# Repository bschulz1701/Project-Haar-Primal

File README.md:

# Project-Haar-Primal
A minimal temp/pressure/RH sensor designed for environmental monitoring. Built off the [Haar](https://github.com/NorthernWidget-Skunkworks/Project-Haar) system, developed by Bobby Schulz at Northern Widget 

# Repo Roadmap
#### [Documents](Documents/) 

General document and image storage for repo and README

#### [Hardware](Hardware/)

Current board files (Eagle), Bill of Materials (BoM), and other design documents

#### [Production](Production/)

Contains the various Gerber and pick and place files required to have the Printed Circuit Boards (PCBs) manufactured or populated 

#### [Software](Software/)

The software associated with the piece of hardware, this is usually diagnostic software used for verifying or investigating the hardware

#### [Mechanical](Mechanical/)

Mechanical design files and assembly documents

<!-- #### [Testing](Testing/)

Scripts and results from the testing process and development process. Contains more detailed information about documented issues among other testing. 
 -->

## Overview
* **Type:** Sensor
* **Interfaces:** I<sup>2</sup>C
* **Release Version:** v2.0 - 2022/03/17

<!--  -->

## Features
### On-Board
* Selectable Pullups
* Reverse Polarity Protection  

### Interface
* I<sup>2</sup>C
* M12 circular connector 

<picture>
  <source media="(prefers-color-scheme: dark)" srcset="Documents/Pinout_LIGHT.png">
  
</picture>

## Specifications
* **Voltage - Supply:** 3.3V
* **Voltage - Logic:** 3.3V
* **Input Current (Avg, 1s period): 30.95&mu;A @ 3.3V**
* **Input Current (Avg, 5s period): 107.43&mu;A @ 3.3V**
* **Input Current (Max): 0.45mA @ 3.3V**

#### Sensor
**Temperature** [^1]
* Range: -40 ~ 125°C 
* Accuracy: &plusmn; 0.2°C
* Repeatability: &plusmn; 0.04°C

**Pressure** [^2]
* Range: 300 ~ 1200 hPa  
* Accuracy: &plusmn; 1 hPa
* Repeatability: &plusmn; 0.06 hPa

**Humidity** [^1]
* Range: 0 ~ 100%
* Accuracy: &plusmn; 2%
* Repeatability: 0.08%

[^1]: [SHT31 Datasheet](https://sensirion.com/media/documents/213E6A3B/63A5A569/Datasheet_SHT3x_DIS.pdf)
[^2]: [DPS368 Datasheet](https://www.infineon.com/dgdl/Infineon-DPS368-DS-v01_00-EN.pdf?fileId=5546d46269e1c019016a0c45105d4b40)

## Version History

`v0.0` - Initial primal version with screw terminal

`v0.1` - Initial 'hard mount' version, using M12 connector

`v1.0` - Removed pullup select[^3], added logic level buffer and voltage reg on input

`v1.1` - Moved via away from connector pads to prevent bridging when soldering 

`v2.0` - Fixed issue with address select jumper[^3]

## Jumper Settings 

> [!IMPORTANT]
> Jumper settings valid for version `v2.0` and beyond[^3]

[^3]: See Errata

**Configuration Jumpers**
| Jumper | Purpose | Open | Closed | Default | 
| ------ | ------- | ---------- | ---------- | ----- | 
| `JP1` | I<sup>2</sup>C Address Select | Base Address<sup>&dagger;</sup> | Alt Address<sup>&Dagger;</sup> | Open |

&dagger; SHT31 = `0x44`, DPS368 = `0x76`

&Dagger; SHT31 = `0x44`, DPS368 = `0x77`

## Known Issues/Errata

#### Solder Jumper Stencil

**Version Affected:** All

**Issue:** Depending on the thickness of the solder stencil used for populating the board, the solder jumpers may not bridge when desired. This is due to lack of stencil thickness specification and pad geometry.

**Workaround:** Make a note on the board assembly (if working with a board house) as to which jumpers should be connected (see jumper tables). Otherwise, if assembling manually, check the jumpers are connected, and bridge them using solder wire and a soldering iron if they have failed to jump where desired. 

#### Pullup Jumper

**Version Affected:** `v0.0`

**Issue:** Due to the resistor configuration with the solder jumper, if the jumper is left open, the resistors form a voltage divider which pulls down the I<sup>2</sup>C rails and causes a variety of bus failures.

**Workaround:** Leave jumper closed on device, this will pull the lines up to the 3.3V rail and prevent the issue 

**Resolution:** Fixed in version `v0.1` and beyond  

#### Address Jumper

**Version Affected:** `v0.1` to `v1.1`

**Issue:** `SDO` pin on DSP368 was erroniously left floating, meaning the DPS368 is continually fixed at the address of `0x76` and will not be effected by the address jumper status

**Workaround:** Leave jumper closed on device, this will hold the SHT31 at the default address as well and keep the address combination consistent 

**Resolution:** Fixed in version `v2.0` and beyond

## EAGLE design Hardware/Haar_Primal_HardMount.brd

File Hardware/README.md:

# Hardware Overview - Project Hyena

## Files

<!-- * [Legacy](Legacy/) - File storage for older hardware versions   -->
* Haar_Primal.sch - Eagle Schematic
* Haar_Primal.brd - Eagle Board File
* [Haar_Primal_0v0_DimensionalDrawing.pdf](Haar_Primal_0v0_DimensionalDrawing.png) - Mechanical Drawing
<!-- * [PrimaryLogger_BoM.csv](PrimaryLogger_BoM.csv) - BoM (For reference only, see [Production](../Production) for production ready BoM) -->
<!-- * [PrimaryLogger.pdf](PrimaryLogger_0v2.pdf) - PDF of Schematic  -->

## I2C Addresses 

| Device | Address | 
| ------ | ------- | 
| DPS368 | 0x77 | 
| SHT30 | 0x44 |

<!-- ## Pinout

| Particle Pin | Hyena Pin Name | Control | Function | 
| ------------ | -------------- | ------- | -------- |
| 8 | `3V3_EXT_EN` | Output | Enables the external 3.3v rail (active high, nominally low) | 
| 7 | `WD_HOLD` | Output | Controls the hardware watchdog timer, pulse high to "feed" timer |
| 6 | `GPIO1D` | IO | General digital IO pin for external sensors (J1 Connector) | 
| 5 | `GPIO2D` | IO | General digital IO pin for external sensors (J2 Connector) | 
| 4 | `GPIO3D` | IO | General digital IO pin for external sensors (J3 Connector) | 
| 3 | `RTC_INT` | Input | Interrupt line from RTC, natively high active low (open drain), triggers on falling edge |
| 2 | `SDA_CTRL` | Output | Used to turn internal I2C on or off (active high, I2C_OB on, natively low) |
| 1 | `SCL` | Output | I2C clock line |
| 0 | `SDA` | IO | I2C Data line |
| 9 | `3V3_SD_EN` | Output | Enable line for SD card 3.3v supply (active high, natively low) |
| 10 | `IO_EXP_INT` | Input | Global interrupt from the IO expander (functionality configurable via software) |
| 11 | `MISO` | Input | MasterInSlaveOut, part of SPI bus |
| 12 | `MOSI` | Output | MasterOutSlaveIn, part of SPI bus | 
| 13 | `SCK` | Output | SerialClocK, part of SPI bus | 
| 14 | `SD_CS` | Output | SD chip select line, active low |
| 15/ADC4 | `TIP` | IO | Designed as tipping bucket rain gauge input, connected to J6, pulled high by default |
| 16/ADC3 | `GPIOXA` | IO | Intended as analog input for potentiometric input (J5) |
| 17/ADC2 | `GPIO1A` | IO | General digital/analog IO pin for external sensors (J1 Connector) |
| 18/ADC1 | `GPIO2A` | IO | General digital/analog IO pin for external sensors (J2 Connector) |
| 19/ADC0 | `GPIO3A` | IO | General digital/analog IO pin for external sensors (J3 Connector) |

| IO Expander Pin | Hyena Pin Name | Control | Function |
| --------------- | -------------- | ------- | -------- |
| 0 | `3V3_EXT_FAULT` | Input | Monitor pin for external 3v3 rail, if over current trip, pin is pulled low, natively high |
| 1 | `3V3_SD_FAULT` | Input | Monitor pin for SD card 3v3 rail, if over current trip, pin is pulled low, natively high |
| 2 | `SD_CD` | Input | Card detect pin for SD card, natively high, pulled low to indicate physical presence of SD card | 
| 3 | `I2C_EXT_EN` | Output | Control line for external I2C buffer, natively high (on), can be pulled low to turn off the external I2C bus | 
| 4 | `PAR_INT` | Input | Event interrupt line from TCS3400 light sensor (used for PAR measurement), active low interrupt |

## Hardware Testing:
See Testing sub folder -->

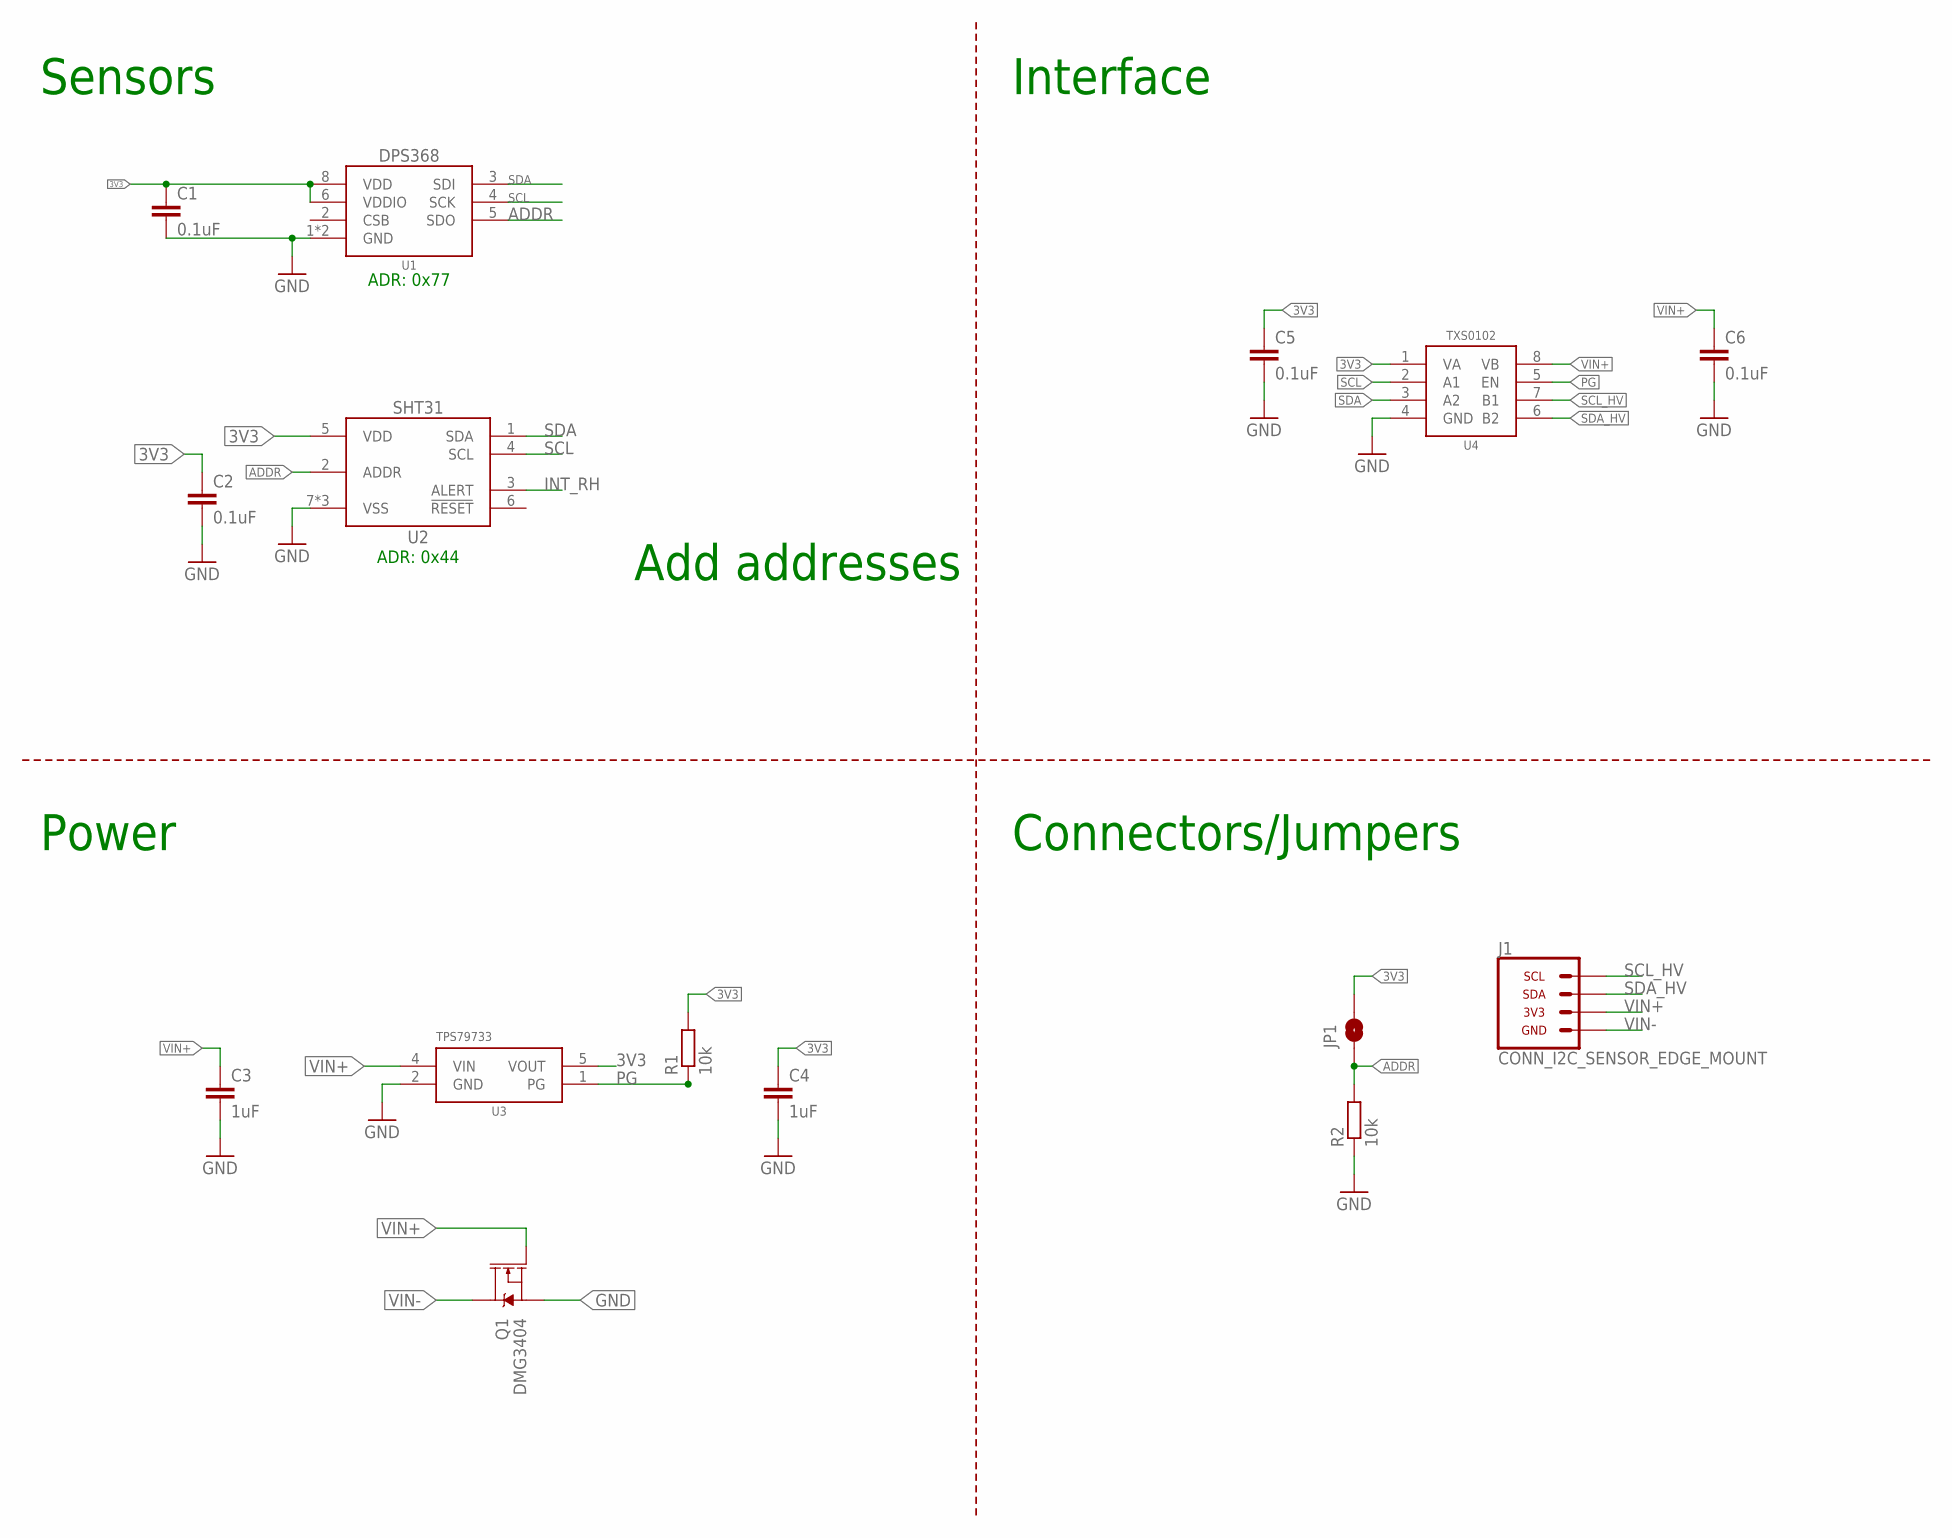
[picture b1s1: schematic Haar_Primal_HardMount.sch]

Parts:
C1, C2, C5, C6: 0.1uF; C0603
C3, C4: 1uF; C0603
J1: CONN_I2C_SENSOR_EDGE_MOUNT; SOLDERCUP_CONN_QUAD
JP1: JUMPER-SMT_2_NO_SILK; SMT-JUMPER_2_NO_SILK
Q1: DMG3404; SOT23-3
R1, R2: 10k; R0603
U1: DPS368; PG-VLGA-8
U2: SHT31DFN; DFN_8_2.5X2.5
U3: TPS79733; DCK_R-PDSO-G5
U4: TXS0102DQM; DQM_R-PX2SON-N8

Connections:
3V3: C1.1, C2.1, C4.1, C5.1, JP1.2, R1.2, U1.6 (VDDIO), U1.8 (VDD), U2.5 (VDD), U3.5 (VOUT), U4.1 (VA)
ADDR: JP1.1, R2.2, U1.5 (SDO), U2.2 (ADDR)
GND: C1.2, C2.2, C3.2, C4.2, C5.2, C6.2, Q1.2 (S), R2.1, U1.1 (GND), U1.7 (GND), U2.7 (VSS), U2.8 (VSS), U2.EP (VSS), U3.2 (GND), U4.4 (GND)
INT_RH: U2.3 (ALERT)
PG: R1.1, U3.1 (PG), U4.5 (EN)
SCL: U1.4 (SCK), U2.4 (SCL), U4.2 (A1)
SCL_HV: J1.3 (SCL), U4.7 (B1)
SDA: U1.3 (SDI), U2.1 (SDA), U4.3 (A2)
SDA_HV: J1.1 (SDA), U4.6 (B2)
VIN+: C3.1, C6.1, J1.2 (3V3), Q1.1 (G), U3.4 (VIN), U4.8 (VB)
VIN-: J1.4 (GND), Q1.3 (D)

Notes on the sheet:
Sensors
Interface
Power
Connectors/Jumpers
Add addresses
ADR: 0x44
ADR: 0x77

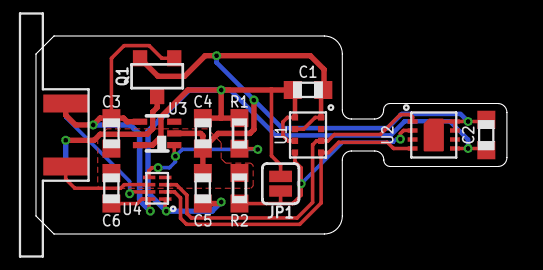
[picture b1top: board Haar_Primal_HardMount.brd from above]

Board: 2 copper layers, 26.2 x 11.0 mm, 15 parts (0 on the bottom side), 10 nets.

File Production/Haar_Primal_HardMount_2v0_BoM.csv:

"Qty","Value","Device","Package","Parts","Description","DIGIKEY","DISP","MF","MPN","VALUE","VALUE_PART",
"4","0.1uF","C-EU0.1UFC0603","C0603","C1, C2, C5, C6","CAPACITOR, European symbol","490-6051-1-ND","","Murata","GCM188R71E104KA57D","","",
"2","10k","R-EU_100KR0603","R0603","R1, R2","RESISTOR, European symbol","311-100KHRCT-ND","","Yageo","RC0603FR-07100KL","","100k",
"2","1uF","C-EU1UFC0603","C0603","C3, C4","CAPACITOR, European symbol","587-1251-1-ND","","Yaiyo Yuden","EMK107BJ105KA-T","","",
"1","CONN_I2C_SENSOR_EDGE_MOUNT","CONN_I2C_SENSOR_EDGE_MOUNT","SOLDERCUP_CONN_QUAD","J1","GEMS Connector for I2C Devices - Sensor Side","A97650-ND","","TE Connectivity","1838893-2","","",
"1","DMG3404","MOSFET-NCH-DMG3404L","SOT23-3","Q1","N-channel MOSFETs","DMG3404L-7DICT-ND","","Diodes Incorporated","DMG3404L-7","DMG3404","",
"1","DPS368","DPS368","PG-VLGA-8","U1","DPS368 - Digital Pressure Sensor","DPS368XTSA1CT-ND","DPS368","Infineon","DPS368XTSA1","","",
"1","JUMPER-SMT_2_NO_SILK","JUMPER-SMT_2_NO_SILK","SMT-JUMPER_2_NO_SILK","JP1","Normally open jumper","DNP","","N/A","N/A","","",
"1","SHT31DFN","SHT31DFN","DFN_8_2.5X2.5","U2","SHT3x - Digital Humidity and Temperature Sensor","1649-1066-1-ND","SHT31","Sensirion","SHT31-DIS-F2.5KS","","",
"1","TPS79733","TPS79733","DCK_R-PDSO-G5","U3","TPS797* - Ultra Low Power Low Dropout Linear Regulator","296-11990-1-ND","TPS79733","TI","TPS79733DCKR","","",
"1","TXS0102DQM","TXS0102DQM","DQM_R-PX2SON-N8","U4","TXS0102 - 2 Channel Bidirectional Voltage Level Translator","296-28435-1-ND","","TI","TXS0102DQMR","","",

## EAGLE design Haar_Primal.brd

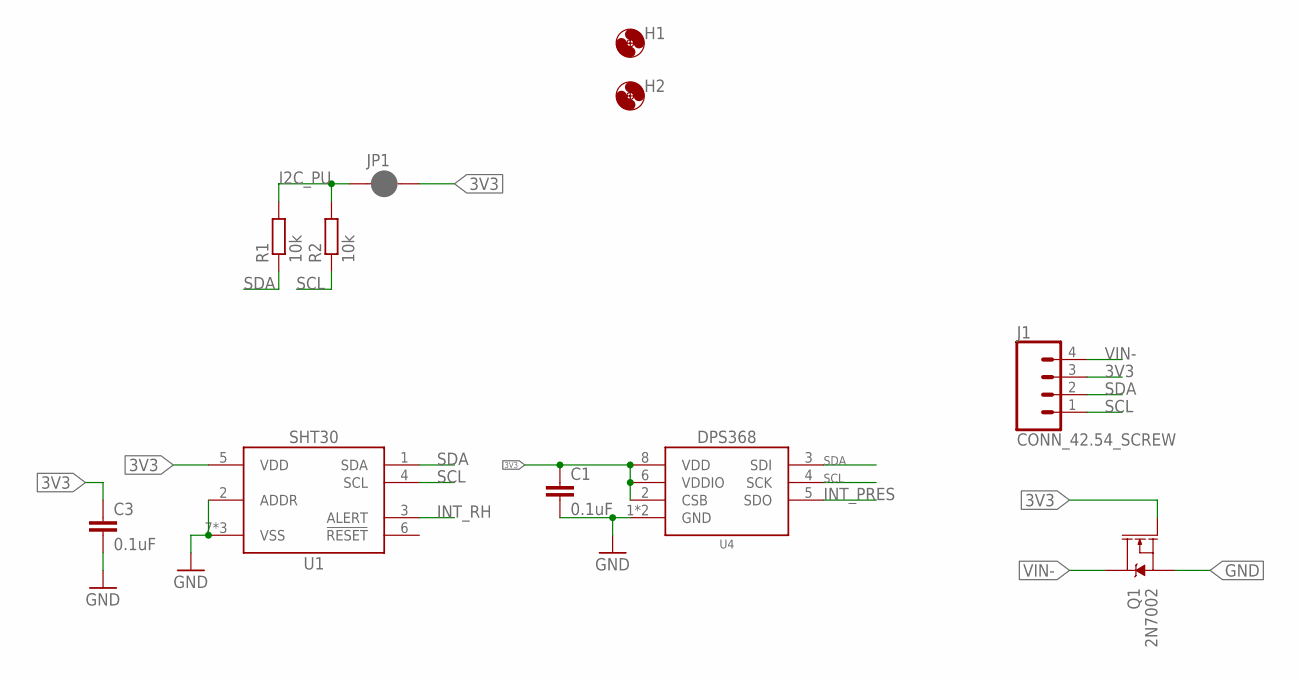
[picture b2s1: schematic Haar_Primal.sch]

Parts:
C1, C3: 0.1uF; C0603
H1, H2: MOUNTING_HOLE2_NP; 2_56
J1: CONN_42.54_SCREW; 1X04_SCREW
JP1: JUMPER-SMT_2_NC_PASTE_SILK; SMT-JUMPER_2_NC_PASTE_SILK
Q1: 2N7002; SOT323
R1, R2: 10k; R0603
U1: SHT30DFN; DFN_8_2.5X2.5
U4: DPS368; PG-VLGA-8

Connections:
3V3: C1.1, C3.1, J1.3, JP1.2, Q1.1 (G), U1.5 (VDD), U4.2 (CSB), U4.6 (VDDIO), U4.8 (VDD)
GND: C1.2, C3.2, Q1.2 (S), U1.2 (ADDR), U1.7 (VSS), U1.8 (VSS), U1.EP (VSS), U4.1 (GND), U4.7 (GND)
I2C_PU: JP1.1, R1.2, R2.2
INT_PRES: U4.5 (SDO)
INT_RH: U1.3 (ALERT)
SCL: J1.1, R2.1, U1.4 (SCL), U4.4 (SCK)
SDA: J1.2, R1.1, U1.1 (SDA), U4.3 (SDI)
VIN-: J1.4, Q1.3 (D)

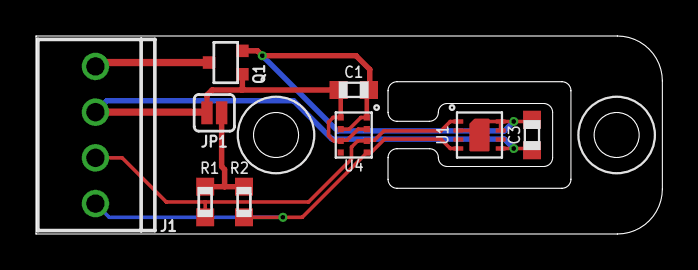
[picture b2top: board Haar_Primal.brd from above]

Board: 2 copper layers, 34.8 x 11.0 mm, 11 parts (0 on the bottom side), 6 nets.

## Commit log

2020-03-19 Updating from local development
    Create seperate repo and update from local development, v0.0 already constructed and tested
2020-04-22 Generated BoM
2020-07-07 Added dimentional drawing
2020-12-21 Updated documentation to match standard
    Updated docs and readmes, need to add photos of board
2021-04-07 Hard mount v0.1 addition
    Added hard mount version and made v0.1 updates to design
2021-04-09 Updated Hard Mount - Variable address jumper
    Added jumper to Hard Mount to allow for a variable address configuration
2021-04-14 Generated gerber for v0.1 Hard Mount
2022-02-11 Added Haar Primal
2022-02-11 Added pick and place and quote files for v0.1 Hard Mount
2022-02-11 Added v1.0 Hard Mount and basic serial demo
2022-02-11 Hard Mount v1.1 Update
2022-02-11 v2.0 Updates - Generated Gerbers
    Fixed ADDR pinout to DPS368
2022-03-17 Updated passive values for v2.0
    Updated some passives and added BoM and mnt
2022-03-30 Create LICENSE
2022-12-19 Cleaned up folders
2024-08-22 Added documentation to README and mechanical files
    Added significant documentation to the README
    - Pinout diagram
    - Updated photo
    - Updated specs
    - Updated jumper info
    - Resolved errata
2024-08-23 Fixed transparency on Haar cutout
2024-08-26 Updated readme for version history and clarified errata
2024-08-27 Added Zenodo link to markdown
2024-11-02 Added documentation, mechanical parts, and demo code

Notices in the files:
parts and their libraries:
SparkFun-Jumpers: Licensing: Creative Commons ShareAlike 4.0 International - https://creativecommons.org/licenses/by-sa/4.0
bschulz: This work is licensed under the Creative Commons Attribution-ShareAlike 4.0
http://creativecommons.org/licenses/by-sa/4.0
